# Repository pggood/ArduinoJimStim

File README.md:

# ArduinoJimStim an Arduino implementation of the JimStim used for megasquirt

A pattern based ignition emulator with 44 common ignition and cam patterns . 

The patterns are in 

wheels_default.h 

Each pattern is a sequence where the first digit is the ignition and cam pulse and the second is the number of degrees it applies for .

The sequence is terminated with 0xff,0, where it loops Back to the beginning.

As it is writing directly to PORTB you could potentially have up to 6 outputs in the pattern.

- 00 is all off
- 01 is ignition on cam off
- 02 is cam on ignition off
- 03 is both cam and ignition on

These patterns can either be for 360 degrees or 720 degrees.

If you are constructing a pattern be careful to add up all the degrees in the second field and make sure it adds up to either 360 or 720

This can be done in a spreadsheet first.

The repository holds the Ardunio source code as well as the Kicad PCB Schematic and gerber files that can be made by people like pcbway, jlcpcb or whoever you preferred PCB maker is. The design is through hole so can be put together by a hobbyist with basic soldering skills.

This is completely open source so do with it as you wish however it is provided on the basis that you use it with your best skill and knowledge and may contain bugs

Wheel Number|DIP Switch  |Wheel Mode                       |Type              |Cam Signal
------------|------------|---------------------------------|------------------|----------  
0           |000000      |Distributor/EDIS|Distributor/EDIS|                  |
1           |000001      |36-1                             |36-1              |X
2           |000010      |60-2                             |60-2              |X
3           |000011      |4-1                              |4-1               |X
4           |000100      |24/2 (Nippondenso)               |24/2 (Nippondenso)|X
5           |000101      |NGC 4 cyl. 36-1+1                |NGC 4 cyl. 36-1+1 |X
6|000110|36-2-2-2|36-2-2-2|X
7|000111|6-1|6-1|X
8|001000|Neon/420A|Neon/420A|X
9|001001|LS1|24+rising/falling (LS1)|X
10|001010|12-1|12-1|X
11|001011|Subaru 6/7|Subaru 6/7|X
12|001100|Trigger return|Trigger return dizzy|
13|001101|Oddfire VR|Oddfire dizzy|
14|001110|Mitsubishi 6G72|Mitsubishi 6G72|X
16|010000|CAS 4/1|4/1 CAS|X
17|010001|4G63|4G63 (Miata)|X
18|010010|Renix 44-2-2|Renix 44-2-2|
19|010011|Twin trigger even|Twin trigger even|X
20|010100|Twin trigger odd|Twin trigger odd|X
21|010101|Suzuki Swift|Suzuki Swift|
22|010110|Suzuki Vitara 2.0|Suzuki Vitara 2.0|
23|010111|Daihatsu 3 cyl|Daihatsu 3 cyl|
24|011000|Daihatsu 4 cyl|Daihatsu 4 cyl|
25|011001|Miata 99-00|Miata 99-00|X
26|011010|Rover 36-1-1|Rover 36-1-1|X
27|011011|Rover 36-1-1-1-1|Rover 36-1-1-1-1|X
28|011100|Rover 36-2-2|Rover 36-2-2|X
29|011101|Honda RC51|Honda RC51|X
30|011110|Chrysler 2.2/2.5|Chrysler 2.2/2.5|X
31|011111|Do not select this|Do not select this|
32|100000|GM 7x native|GM 7x native|
33|100001|32-2 Harley|32-2 Harley|
34|100010|6/1|6/1|X
35|100011|8/1|8/1|X
36|100100|10/1|10/1|X
37|100101|Honda VTR1000 12-3|Honda VTR1000 12-3|
38|100110|IAW Weber-Marelli|IAW Weber-Marelli|X
39|100111|Fiat 1.8 16V|Fiat 1.8 16V|X
40|101000|Mitsubishi 360 tooth CAS (6 cyl)|Mitsubishi 360 tooth CAS (6 cyl)|X
41|101001|Mitsubishi 360 tooth CAS (8 cyl)|Mitsubishi 360 tooth CAS (8 cyl)|X
42|101010|4.0 Jeep 2000|4.0 Jeep 2000|X
43|101011|3.7 Jeep 2002|3.7 Jeep 2002|X
44|101100|NGC 6 cyl. 36-1+1|NGC 6 cyl. 36-1+1|X
45|101101|NGC 8 cyl. 36-1+1|NGC 8 cyl. 36-1+1|X

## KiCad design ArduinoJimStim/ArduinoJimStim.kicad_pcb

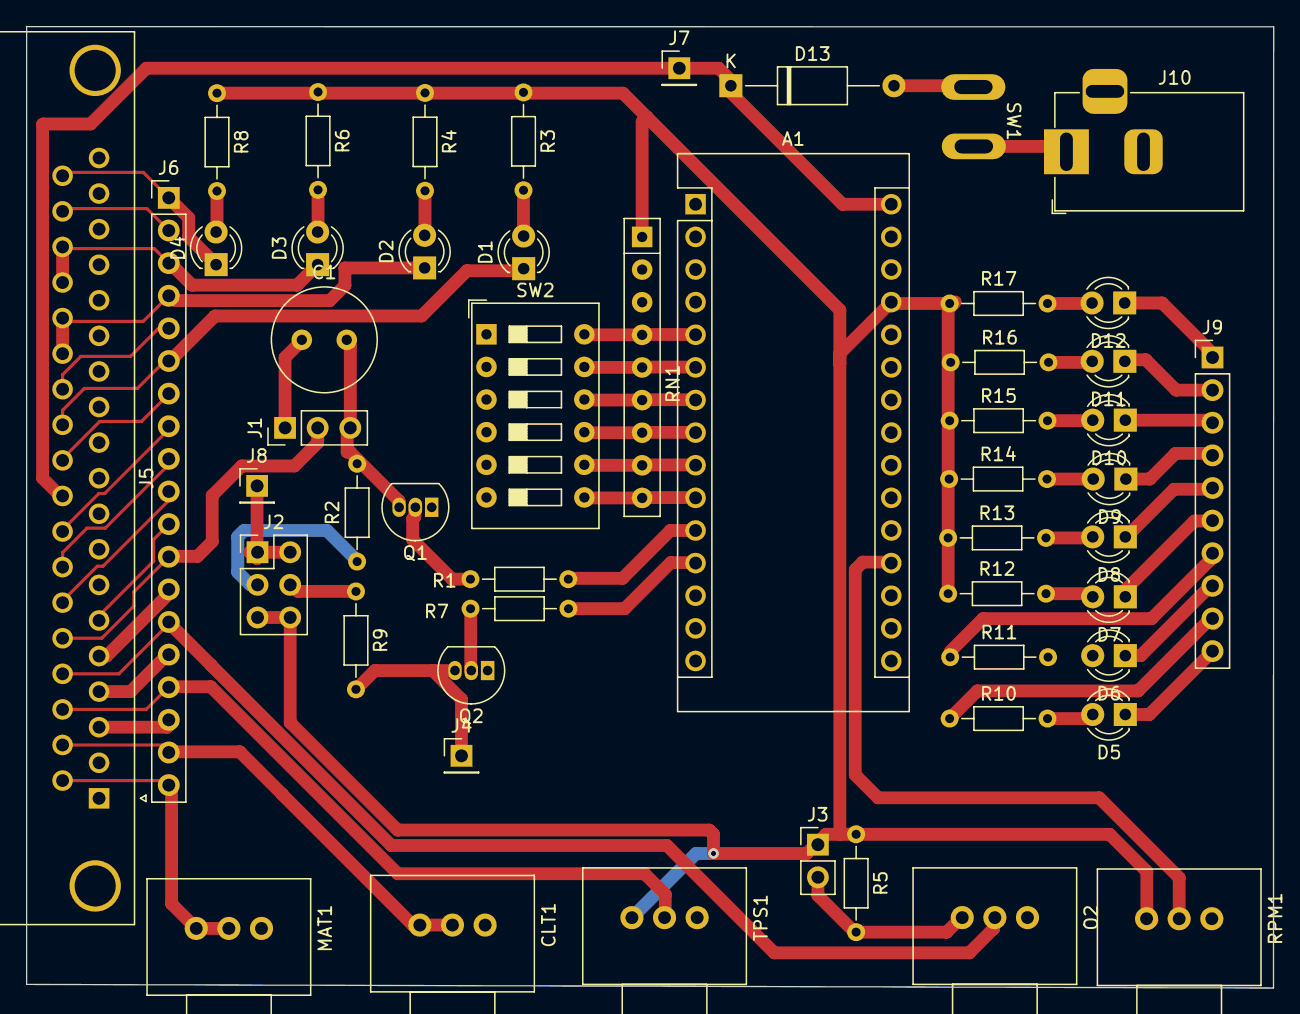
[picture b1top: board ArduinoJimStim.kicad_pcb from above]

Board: 2 copper layers, 97.1 x 74.9 mm, 52 parts (0 on the bottom side), 64 nets.

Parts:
A1: Arduino_Nano_v3.x; Arduino_Nano
C1: 100n; C_Radial_D8.0mm_H11.5mm_P3.50mm
CLT1: 10K; Potentiometer_Vishay_148-149_Single_Horizontal
D1, D2, D3, D4, D5, D6, D7, D8, D9, D10, D11, D12: LED; LED_D3.0mm_Clear
D13: D; D_A-405_P12.70mm_Horizontal
J1: TACH; PinHeader_1x03_P2.54mm_Vertical
J2: Conn_02x03_Odd_Even; PinHeader_2x03_P2.54mm_Vertical
J3: O2; PinHeader_1x02_P2.54mm_Vertical
J4: 2ND Trigger; PinHeader_1x01_P2.54mm_Vertical
J5: DB37_Male; DSUB-37_Female_Horizontal_P2.77x2.84mm_EdgePinOffset4.94mm_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
J6: Conn_01x19_Male; PinHeader_1x19_P2.54mm_Vertical
J7, J8: 12v; PinHeader_1x01_P2.54mm_Vertical
J9: Conn_01x10_Female; PinHeader_1x10_P2.54mm_Vertical
J10: Barrel_Jack; BarrelJack_Horizontal
MAT1: 10K; Potentiometer_Vishay_148-149_Single_Horizontal
O2: 10K; Potentiometer_Vishay_148-149_Single_Horizontal
Q1, Q2: 2N3904; TO-92_Inline
R1, R2, R5, R7, R9: 1K; R_Axial_DIN0204_L3.6mm_D1.6mm_P7.62mm_Horizontal
R3, R4, R6, R8, R10, R11, R12, R13, R14, R15, R16, R17: 330; R_Axial_DIN0204_L3.6mm_D1.6mm_P7.62mm_Horizontal
RN1: R_Network08_US; R_Array_SIP9
RPM1: 10K; Potentiometer_Vishay_148-149_Single_Horizontal
SW1: SW_SPST; MTS-101_SPST
SW2: SW_DIP_x06; SW_DIP_SPSTx06_Slide_9.78x17.42mm_W7.62mm_P2.54mm
TPS1: 10K; Potentiometer_Vishay_148-149_Single_Horizontal

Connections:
GND: A1.4 (GND), A1.29 (GND), CLT1.3, J5.1, J5.2, J5.7, J5.8, J5.9, J5.10, J5.11, J5.19, J10.2, MAT1.3, O2.3, Q1.1 (E), Q2.1 (E), RPM1.3, SW2.1, SW2.2, SW2.3, SW2.4, SW2.5, SW2.6, TPS1.3
unnamed: A1.5 (D2), RN1.4 (R3), SW2.12
unnamed: A1.6 (D3), RN1.5 (R4), SW2.11
unnamed: A1.7 (D4), RN1.6 (R5), SW2.10
unnamed: A1.8 (D5), RN1.7 (R6), SW2.9
unnamed: A1.9 (D6), RN1.8 (R7), SW2.8
unnamed: A1.10 (D7), RN1.9 (R8), SW2.7
unnamed: A1.11 (D8), R1.1
unnamed: A1.12 (D9), R7.1
unnamed: A1.19 (A0), RPM1.2
unnamed: A1.27 (+5V), J2.5, J2.6, J3.1, R3.1, R4.1, R5.1, R6.1, R8.1, R12.1, R13.1, R14.1, R15.1, R16.1, R17.1, RN1.1 (common), RPM1.1, TPS1.1
unnamed: A1.30 (VIN), D13.1 (K), J5.28, J7.1
unnamed: C1.1, J1.1
unnamed: C1.2, J1.3, Q1.3 (C), R2.2
unnamed: CLT1.1, CLT1.2, J5.21, J6.18
unnamed: D1.1 (K), J5.30, J6.6
unnamed: D1.2 (A), R3.2
unnamed: D2.1 (K), J5.32, J5.33, J6.4
unnamed: D2.2 (A), R4.2
unnamed: D3.1 (K), J5.34, J5.35, J6.3
unnamed: D3.2 (A), R6.2
unnamed: D4.1 (K), J5.37, J6.1
unnamed: D4.2 (A), R8.2
unnamed: D5.1 (K), J9.10
unnamed: D5.2 (A), R10.2
unnamed: D6.1 (K), J9.8
unnamed: D6.2 (A), R11.2
unnamed: D7.1 (K), J9.6
unnamed: D7.2 (A), R12.2
unnamed: D8.1 (K), J9.5
unnamed: D8.2 (A), R13.2
unnamed: D9.1 (K), J9.4
unnamed: D9.2 (A), R14.2
unnamed: D10.1 (K), J9.3
unnamed: D10.2 (A), R15.2
unnamed: D11.1 (K), J9.2
unnamed: D11.2 (A), R16.2
unnamed: D12.1 (K), J9.1
unnamed: D12.2 (A), R17.2
unnamed: D13.2 (A), SW1.1 (A)
unnamed: J1.2, J5.24, J6.12
unnamed: J2.1, J2.2, J8.1
unnamed: J2.3, R2.1
unnamed: J2.4, R9.1
unnamed: J3.2, O2.1, R5.2
unnamed: J4.1, Q2.3 (C), R9.2
unnamed: J5.3, J6.17
unnamed: J5.4, J6.15
unnamed: J5.5, J6.13
unnamed: J5.6, J6.11
unnamed: J5.20, J6.19, MAT1.1, MAT1.2
unnamed: J5.22, J6.16, TPS1.2
unnamed: J5.23, J6.14, O2.2
unnamed: J5.25, J6.10
unnamed: J5.26, J6.9
unnamed: J5.27, J6.8
unnamed: J5.29, J6.7
unnamed: J5.31, J6.5
unnamed: J5.36, J6.2
unnamed: J9.7, R11.1
unnamed: J9.9, R10.1
unnamed: J10.1, SW1.2 (B)
unnamed: Q1.2 (B), R1.2
unnamed: Q2.2 (B), R7.2

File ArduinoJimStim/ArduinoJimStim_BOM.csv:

"Id";"Designator";"Package";"Quantity";"Designation";"Supplier and ref";
1;"RN1";"R_Array_SIP9";1;"R_Network08_US";;;
2;"D2,D8,D4,D5,D1,D6,D11,D10,D9,D7,D12,D3";"LED_D3.0mm_Clear";12;"LED";;;
3;"J10";"BarrelJack_Horizontal";1;"Barrel_Jack";;;
4;"R10,R15,R17,R12,R14,R13,R16,R4,R11,R6,R3,R8";"R_Axial_DIN0204_L3.6mm_D1.6mm_P7.62mm_Horizontal";12;"330";;;
5;"J4";"PinHeader_1x01_P2.54mm_Vertical";1;"2ND Trigger";;;
6;"C1";"C_Radial_D8.0mm_H11.5mm_P3.50mm";1;"100n";;;
7;"J3";"PinHeader_1x02_P2.54mm_Vertical";1;"O2";;;
8;"J8,J7";"PinHeader_1x01_P2.54mm_Vertical";2;"12v";;;
9;"D13";"D_A-405_P12.70mm_Horizontal";1;"D";;;
10;"J5";"DSUB-37_Female_Horizontal_P2.77x2.84mm_EdgePinOffset4.94mm_Housed_MountingHolesOffset7.48mm";1;"DB37_Male";;;
11;"MAT1,CLT1,RPM1,O2,TPS1";"Potentiometer_Vishay_148-149_Single_Horizontal";5;"10K";;;
12;"Q2,Q1";"TO-92_Inline";2;"2N3904";;;
13;"R5,R1,R2,R7,R9";"R_Axial_DIN0204_L3.6mm_D1.6mm_P7.62mm_Horizontal";5;"1K";;;
14;"J1";"PinHeader_1x03_P2.54mm_Vertical";1;"TACH";;;
15;"J2";"PinHeader_2x03_P2.54mm_Vertical";1;"Conn_02x03_Odd_Even";;;
16;"SW1";"MTS-101_SPST";1;"SW_SPST";;;
17;"A1";"Arduino_Nano";1;"Arduino_Nano_v3.x";;;
18;"J9";"PinHeader_1x10_P2.54mm_Vertical";1;"Conn_01x10_Female";;;
19;"SW2";"SW_DIP_SPSTx06_Slide_9.78x17.42mm_W7.62mm_P2.54mm";1;"SW_DIP_x06";;;
20;"J6";"PinHeader_1x19_P2.54mm_Vertical";1;"Conn_01x19_Male";;;

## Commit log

2022-06-27 36 missing tooth Arduino ignition emulator
    A simple 36 tooth ignition emulator for Arduino using a pot to vary the RPM
2022-06-27 JimStim for Arduino
    A pattern based ignition emulator with 44 common ignition and cam patterns . The patterns are in wheels_default.h
    Each pattern is a sequence where the first digit is the ignition and cam pulse and the sequence is terminated with 0xff,0, where it loops Back to the beginning.
    As it is writing directly to PORTB you could potentially have up to 6 outputs in the pattern.
    00 is all off
    01 is ignition on cam off
    02 is cam on ignition off
2025-06-02 Basic BOM
